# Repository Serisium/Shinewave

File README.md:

# Overview

Shinewave is a program for the ATtiny85 microcontroller that allows it to decode a live GameCube controller signal and reactively power RGB LEDs based on button inputs.

[More information](http://electricexploits.net/shinewave/)

[Video](https://www.youtube.com/watch?v=1U4EOI_aFdc)

## Installation & Usage

Shinewave has been written on a Linux system and requires the full avr-gcc toolchain to make.

In Debian, the toolchain can be set up with the following commands.

	sudo apt-get install gcc-avr avr-libc avrdude

Then, download the repository to your local machine. 

	git clone git@github.com:GGreenwood/Shinewave.git
    git checkout t85

To build the project, just run `make`, or `make flash` to build and program. You'll probably need to chance the `PROGRAMMER` line in `Makefile` in order to program it directly.

## Wiring

## Dependencies

This project depends on one library

* Josh Levine's simple [NeoPixel Demo](https://github.com/bigjosh/SimpleNeoPixelDemo) library

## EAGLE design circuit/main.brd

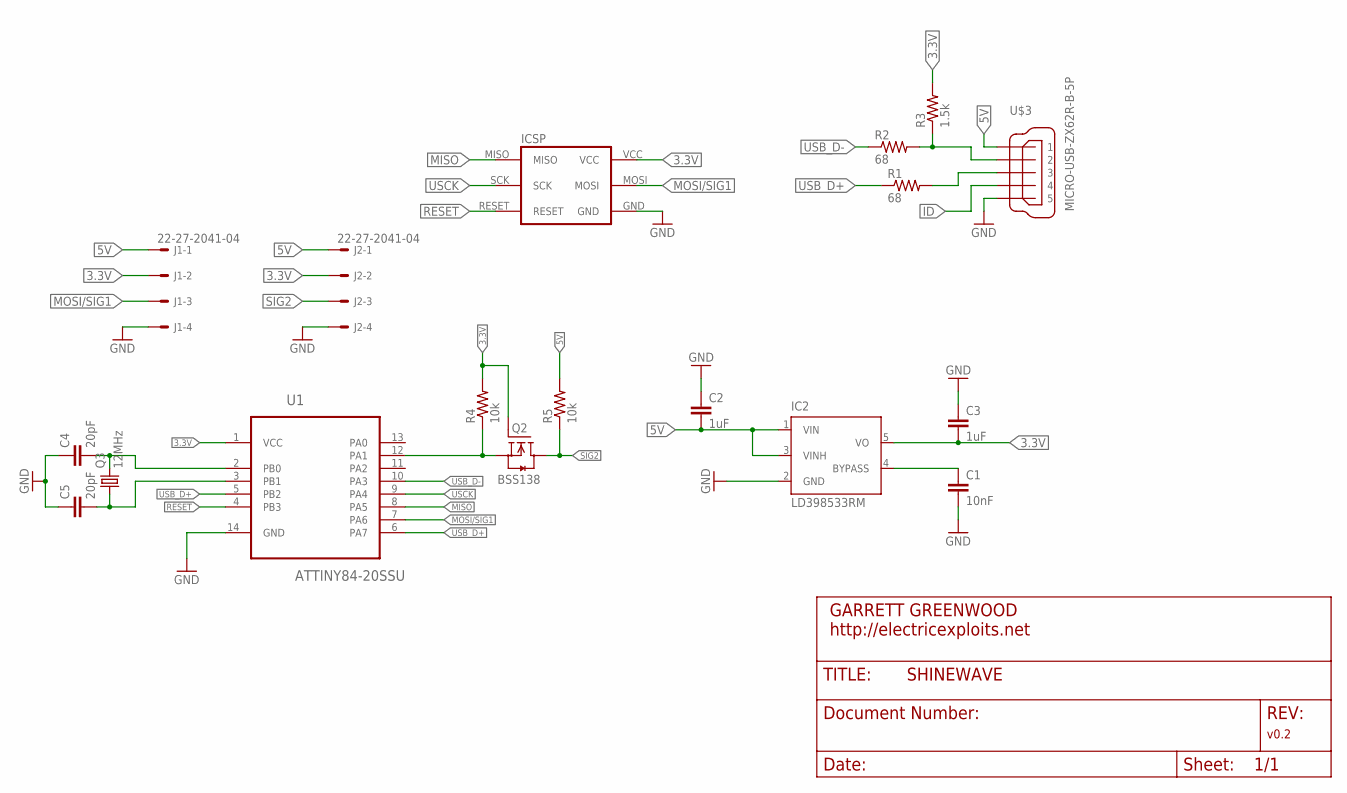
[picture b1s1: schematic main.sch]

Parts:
C1: 10nF; C0603
C2, C3: 1uF; C0603
C4, C5: 20pF; C0603
IC2: LD398533RM; SOT23-5L
J1, J2: 22-27-2041-04; 6410-04
Q2: BSS138; SOT23
Q3: 12MHz; CTS406
R1, R2: 68; R0603
R3: 1.5k; R0603
R4, R5: 10k; R0603
U1: ATTINY84-20SSU; SOIC127P600X175-14N
U$1: ICSP_POGO_INTERFACE; ICSP_SMD
U$3: MICRO-USB-ZX62R-B-5P; ZX62R-B-5P

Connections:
3.3V: C3.2, IC2.5 (VO), J1.2, J2.2, Q2.1 (G), R3.2, R4.2, U1.1 (VCC), U$1.VCC
5V: C2.2, IC2.1 (VIN), IC2.3 (VINH), J1.1, J2.1, R5.2, U$3.1
GND: C1.2, C2.1, C3.1, C4.1, C5.1, IC2.2 (GND), J1.4, J2.4, U1.14 (GND), U$1.GND, U$3.5
ID: U$3.4
MISO: U1.8 (PA5), U$1.MISO
MOSI/SIG1: J1.3, U1.7 (PA6), U$1.MOSI
unnamed: Q2.2 (S), R4.1, U1.12 (PA1)
unnamed: R2.2, R3.1, U$3.2
unnamed: C1.1, IC2.4 (BYPASS)
unnamed: R1.2, U$3.3
RESET: U1.4 (PB3), U$1.RESET
SIG2: J2.3, Q2.3 (D), R5.1
USB_D+: R1.1, U1.5 (PB2), U1.6 (PA7)
USB_D-: R2.1, U1.10 (PA3)
USCK: U1.9 (PA4), U$1.SCK
XTAL1: C4.2, Q3.3 (2), U1.2 (PB0)
XTAL2: C5.2, Q3.1, U1.3 (PB1)

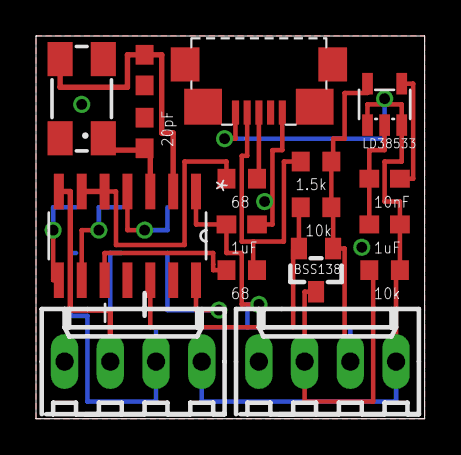
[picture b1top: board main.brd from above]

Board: 2 copper layers, 21.6 x 21.3 mm, 18 parts (0 on the bottom side), 16 nets.

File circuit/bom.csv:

"Part";"Value";"Device";"Package";"Description";"MF";"MPN";"OC_FARNELL";"OC_NEWARK";"PACKAGE";"SUPPLIER";
"C1";"10nF";"C-EUC0603";"C0603";"CAPACITOR, European symbol";"";"";"";"";"";"";
"C2";"1uF";"C-EUC0603";"C0603";"CAPACITOR, European symbol";"";"";"";"";"";"";
"C3";"1uF";"C-EUC0603";"C0603";"CAPACITOR, European symbol";"";"";"";"";"";"";
"C4";"20pF";"C-EUC0603";"C0603";"CAPACITOR, European symbol";"";"";"";"";"";"";
"C5";"20pF";"C-EUC0603";"C0603";"CAPACITOR, European symbol";"";"";"";"";"";"";
"IC2";"LD398533RM";"LD398533RM";"SOT23-5L";"Ultra low drop and low noise BiCMOS voltage regulators";"";"";"";"";"";"";
"J1";"22-27-2041-04";"22-27-2041-04";"6410-04";"CONNECTOR";"";"";"unknown";"unknown";"";"";
"J2";"22-27-2041-04";"22-27-2041-04";"6410-04";"CONNECTOR";"";"";"unknown";"unknown";"";"";
"Q2";"BSS138";"BSS138";"SOT23";"Fairchild Semiconductors BSS138 N-Channel Logic Level Enhancement Mode Field Effect Transistor";"";"";"";"";"";"";
"Q3";"12MHz";"CRYSTALCTS406";"CTS406";"CRYSTAL";"";"";"unknown";"unknown";"";"";
"R1";"68";"R-US_R0603";"R0603";"RESISTOR, American symbol";"";"";"";"";"";"";
"R2";"68";"R-US_R0603";"R0603";"RESISTOR, American symbol";"";"";"";"";"";"";
"R3";"1.5k";"R-US_R0603";"R0603";"RESISTOR, American symbol";"";"";"";"";"";"";
"R4";"10k";"R-US_R0603";"R0603";"RESISTOR, American symbol";"";"";"";"";"";"";
"R5";"10k";"R-US_R0603";"R0603";"RESISTOR, American symbol";"";"";"";"";"";"";
"U$1";"ICSP_POGO_INTERFACE";"ICSP_POGO_INTERFACE";"ICSP_SMD";"ICSP pads for programming over a pogo-pin interface.";"";"";"";"";"";"";
"U$3";"MICRO-USB-ZX62R-B-5P";"MICRO-USB-ZX62R-B-5P";"ZX62R-B-5P";"Hirose Micro USB Connector";"";"";"";"";"";"";
"U1";"ATTINY84-20SSU";"ATTINY84-20SSU";"SOIC127P600X175-14N";"8-bit Microcontroller with Bytes In-System Programmable Flash";"";"ATTINY84-20SSU";"1636955";"03P2040";"SOIC-14";"Atmel";

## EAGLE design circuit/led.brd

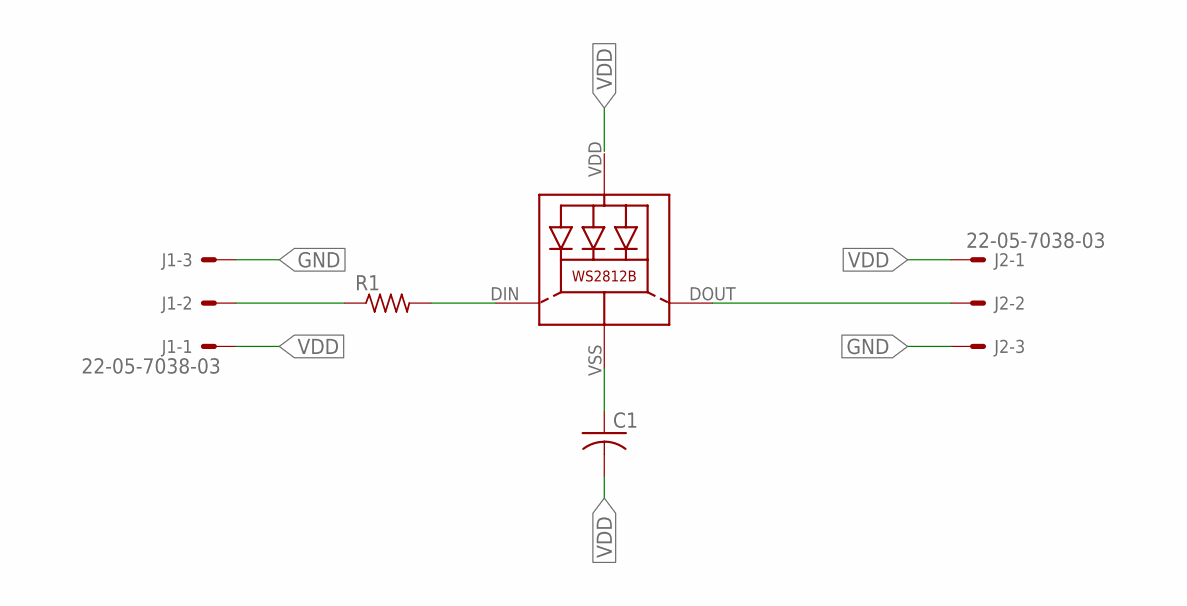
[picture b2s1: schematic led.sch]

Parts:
C1: C-USC0603; C0603
J1, J2: 22-05-7038-03; 7395-03
LED1: WS2812B
R1: R-US_R0603; R0603

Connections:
GND: C1.1, J1.3, J2.3, LED1.VSS (GND)
unnamed: J1.2, R1.1
unnamed: LED1.DIN (DI), R1.2
unnamed: J2.2, LED1.DOUT (DO)
VDD: C1.2, J1.1, J2.1, LED1.VDD

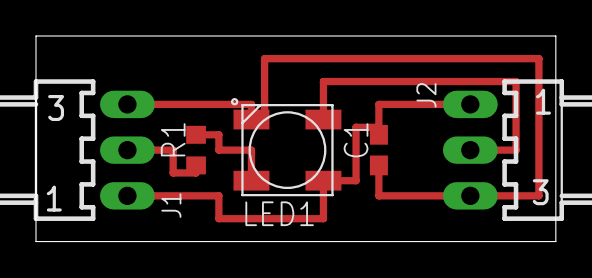
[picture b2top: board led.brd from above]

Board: 2 copper layers, 28.9 x 11.4 mm, 5 parts (0 on the bottom side), 5 nets.

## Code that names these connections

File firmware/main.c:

#include <avr/interrupt.h>
#include <avr/io.h>
#include <avr/wdt.h>
#include <stdint.h>
#include <util/delay.h>

//#include "libs/Neopixel.h"
#include "controller.h"
#include "usb.h"

#define DEBUG_MATCH 0   // Enable PIN_TIMER toggle on timer match. Interferes with USB
#define GCN_RETRY_LIMIT 5   // Number of times to retry the GCN signal line

#define PIN_DEBUG PA2
#define PIN_GC    PA6   // Needs to be connected to (DI)
//#define PIN_TIMER PA7   // Needs to be connected to (OC0B). Displays compare match toggles if DEBUG_MATCH is set

#define GET_BIT(TGT, PIN)    ((TGT) & (1 << (PIN))) 
#define SET_BIT(TGT, PIN)    do { TGT |=  (1 << (PIN)); } while(0)
#define CLEAR_BIT(TGT, PIN)  do { TGT &= ~(1 << (PIN)); } while(0)
#define TOGGLE_BIT(TGT, PIN) do { TGT ^=  (1 << (PIN)); } while(0)

#define SEND_ZERO()        do { CLEAR_BIT(PORTA, PIN_GC); _delay_us(3); SET_BIT(PORTA, PIN_GC); _delay_us(1); } while(0)
#define SEND_ONE()         do { CLEAR_BIT(PORTA, PIN_GC); _delay_us(1); SET_BIT(PORTA, PIN_GC); _delay_us(3); } while(0)

void setup_pins(void) {
    CLEAR_BIT(DDRA, PIN_GC);		// Set PIN_GC as input, GCN data signal
    SET_BIT(PORTA, PIN_GC);		    // Enable pull-up resistor on PIN_GC
    SET_BIT(DDRA, PIN_DEBUG);       // Set PIN_DEBUG as output for debugging

    // Ensure that USB pins are inputs with pullup resistor disabled
    CLEAR_BIT(DDRB, PB2);
    CLEAR_BIT(DDRA, PA3);
    CLEAR_BIT(DDRA, PA7);
    CLEAR_BIT(PORTB, PB2);
    CLEAR_BIT(PORTA, PA3);
    CLEAR_BIT(PORTA, PA7);

    #if DEBUG_MATCH == 1
    SET_BIT(DDRA, PIN_TIMER);       // Set PIN_TIMER as output for compare matches
    #endif
    //ledsetup();
}

void enable_timer0(void) {
    TCNT0 = 0;
    TIFR0 = 0xff;                   // Reset interrupt flags

    #if DEBUG_MATCH == 1
    // Set 0C0B(PA7) to toggle on match(COM0B=01)
    SET_BIT(TCCR0A, COM0B0);
    #endif

    // Enable Timer/Counter0 module at no prescaler
    SET_BIT(TCCR0B, CS00);
}

void disable_timer0(void) {
    #if DEBUG_MATCH == 1
    // Set 0C0B(PA7) to toggle on match(COM0B=01)
    CLEAR_BIT(TCCR0A, COM0B0);
    #endif

    // Disable Timer/Counter0 module
    CLEAR_BIT(TCCR0B, CS00);        
}

// Set Timer/Counter0 in normal mode(WGM=000)
void setup_timer0(void) {
    disable_timer0();

    // Set compare match to signal critical point(2us)
    OCR0A = 2e-6 * F_CPU;   // Triggers USI clock source

    #if DEBUG_MATCH == 1
    OCR0B = 2e-6 * F_CPU;   // Triggers debug toggle
    #endif
}

void enable_usi(void) {
    // Enable Universal Serial Module in Two-wire mode(USIWM=10)
    SET_BIT(USICR, USIWM1);
}

void disable_usi(void) {
    // Disable Universal Serial Module
    SET_BIT(USICR, USIWM1);
}

void setup_usi(void) {
    // Set clock source to Timer/Counter0 Compare Match(USICS=01)
    SET_BIT(USICR, USICS0);
}

void setup_usb(void) {
    cli();
    wdt_enable(WDTO_1S);    // enable 1s watchdog timer
    usbInit();

    usbDeviceDisconnect();  // enforce re-enumeration
    uint8_t i;
    for(i = 0; i<250; i++) {
        wdt_reset();
        _delay_ms(2);
    }
    usbDeviceConnect();
    sei();
}

void init_controller(void) {
    SET_BIT(PORTA, PIN_GC);         // Set positive output on PIN_GC
    SET_BIT(DDRA, PIN_GC);          // Set PIN_GC as output

    // Send controller init message (000000001)
    for(uint8_t bit = 0; bit < 8; bit++) {
        SEND_ZERO();
    }
    SEND_ONE();

    CLEAR_BIT(DDRA, PIN_GC);        // Set PIN_GC as input
}

uint8_t request_message(uint8_t *message_buffer) {
    //uint8_t cur_byte = 0;

    //USISR = 0b11101000;             // Reset USI Interrupt flags and set timer value to 8
    //disable_usi();
    //disable_timer0();

    CLEAR_BIT(PORTA, PIN_DEBUG);
    SET_BIT(PORTA, PIN_DEBUG);
    CLEAR_BIT(PORTA, PIN_DEBUG);
    
    SET_BIT(PORTA, PIN_GC);
    SET_BIT(DDRA, PIN_GC);          // Set PIN_GC as output

    asm volatile(
            ".rept 3 \n\t"
                "cbi %[port], %[bit] \n\t"
                ".rept 34 \n\t"
                    "nop \n\t"
                ".endr \n\t"
                "sbi %[port], %[bit] \n\t"
                ".rept 10 \n\t"
                    "nop \n\t"
                ".endr \n\t" 
                "cbi %[port], %[bit] \n\t"
                ".rept 10 \n\t"
                    "nop \n\t"
                ".endr \n\t"
                "sbi %[port], %[bit] \n\t"
                ".rept 34 \n\t"
                    "nop \n\t"
                ".endr \n\t" 
            ".endr \n\t"
            ".rept 18 \n\t"
                "cbi %[port], %[bit] \n\t"
                ".rept 34 \n\t"
                    "nop \n\t"
                ".endr \n\t"
                "sbi %[port], %[bit] \n\t"
                ".rept 10 \n\t"
                    "nop \n\t"
                ".endr \n\t"
            ".endr \n\t"
            "cbi %[port], %[bit] \n\t"
            ".rept 10 \n\t"
                "nop \n\t"
            ".endr \n\t"
            "sbi %[port], %[bit] \n\t"
            ".rept 34 \n\t"
                "nop \n\t"
            ".endr \n\t"
            :: 
            [port]      "I" (_SFR_IO_ADDR(PORTA)),
            [bit]       "I" (PA6)
        );

    SET_BIT(PORTA, PIN_GC);
    CLEAR_BIT(DDRA, PIN_GC);        // Set PIN_GC as input
    
    return 1;
    /*

    // Send controller data request
    SEND_ZERO(); SEND_ONE();  SEND_ZERO(); SEND_ONE();  SEND_ZERO(); SEND_ONE();  SEND_ZERO(); SEND_ZERO(); 
    SEND_ZERO(); SEND_ZERO(); SEND_ZERO(); SEND_ZERO(); SEND_ZERO(); SEND_ZERO(); SEND_ZERO(); SEND_ZERO();
    SEND_ZERO(); SEND_ZERO(); SEND_ZERO(); SEND_ZERO(); SEND_ZERO(); SEND_ZERO(); SEND_ZERO(); SEND_ZERO(); 
    SEND_ONE();

    SET_BIT(PORTA, PIN_GC);
    CLEAR_BIT(DDRA, PIN_GC);        // Set PIN_GC as input

    // Start reading the message
    enable_usi();
    enable_timer0();
    while(1) {
        // Wait for signal to go low
        while(GET_BIT(PINA, PIN_GC)) {
            // Catch a timer overflow as an exit condition
            // This occurs if the signal is high for > 255 cycles
            if(GET_BIT(TIFR0, TOV0)) {
                // Exit condition
                disable_usi();

                // Wait for the timer to overflow and loop once, fixes 'every other' corruption
                while(TCNT0 < 24) {}

                // Check if there's no signal on the line
                if(cur_byte == 0) {
                    SET_BIT(PORTA, PIN_DEBUG);
                    CLEAR_BIT(PORTA, PIN_DEBUG);
                    return 0;
                }

                disable_timer0();
                return 1;
            }
        }
        // Reset Timer0, a little higher than 0 to account for polling delay
        TCNT0 = 5;

        // Check if a byte has passed
        if(GET_BIT(USISR, USIOIF)) {
            // Skip the counter to 8 of 16
            SET_BIT(USISR, USICNT3);    

            // Store the byte from the serial buffer
            message_buffer[cur_byte] = USIBR;
            cur_byte++;

            // Toggle the debug pin
            //TOGGLE_BIT(PORTA, PIN_DEBUG);

            // Clear the overflow counter
            SET_BIT(USISR, USIOIF);
        }

        // Make sure signal is high before looping
        // Hardware should pull up DIN or risk an infinite loop
        while(!GET_BIT(PINA, PIN_GC)) {}
    }
    */

    // Unreachable code
    return 0;
}

int main(void)
{
    setup_pins();
    //setup_timer0();
    //setup_usi();
    setup_usb();
    //init_controller();

    uint8_t retry_count = 0;

    uint8_t message_buffer[8] = {0};
    Keyboard *keyboard = (Keyboard*)message_buffer;

    /*
    while(1) {
        request_message(message_buffer);
        for(uint8_t i = 0; i < 16; ++i) {
            wdt_reset();
            usbPoll();
            _delay_ms(1);
        }
    }
    */

    while(1) {
        usbPoll();
        wdt_reset();

        if(usbInterruptIsReady()) {
            // Zero out input array
            for(uint8_t i = 0; i < 8; ++i) {
                message_buffer[i] = 0x00;
            }
            // Try to grab the controller state
            retry_count = GCN_RETRY_LIMIT;
            while(retry_count--) {
                if(request_message(message_buffer)) {
                    build_report(keyboard, &reportBuffer);
                    usbSetInterrupt((void *)&reportBuffer, sizeof(reportBuffer));
                    break;
                }

                _delay_us(50);
            }
        }
    }
}

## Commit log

2015-06-13 Added proof of concept C code implementing mock animation and protothreads
2015-06-18 Added compilation procedure
2015-06-18 Removed swap file
2015-06-18 Wrote proper Makefile
2015-06-24 Rewrote controller reading code to use the Analog Comparator
2015-06-27 Fixed endianness of controller POC definition
2015-06-28 Started work on animation protothread and controller state wrapper
2015-06-29 Added smooth animation lookups and a jump thread
2015-06-30 Added sawtooth function and idle animation
2015-06-30 Fixed jump animation
2015-07-03 Moved saw macro into a function and omitted descending functions
2015-07-03 Delayed idle animation until the controller is actually idle
2015-07-03 Controller can now jump out of neutral
2015-07-03 Controller can now down-air
2015-07-03 Added taunt
2015-07-04 Made down-air shine cancellable
2015-07-13 Added eight brightness levels
2015-07-15 Started work on state machine proof of concept
2015-07-15 fixed output
2015-07-16 progress, or something
2015-07-16 more progress, thanks reid for help
2015-07-16 WEEEEEEEEEEEEEE
2015-07-16 made the code neater and left notes for the morning
2015-07-17 Added exit condition on max frame
2015-07-17 Added single exit condition
2015-08-02 Added comments
2015-08-02 Moved proof of concept demos to its own repo
2015-08-27 added delay loop; needs tested
2015-08-30 Updated project name and added make fuse command
2015-08-31 Rewrote EVERYTHING
2015-08-31 Reduced timer complexity
2015-08-31 Testing control stick driven colors
2015-09-01 Integrated Controller convenience class
2015-09-01 Added reactive wait times; works on GC/Wii
2015-09-02 Implemented new animation state machine, courtesy @JustANull
2015-09-13 Updated indentation
2015-09-21 Microcontroller can now request controller state
2015-09-21 Gamecube controller is now a mouse
2015-09-22 Gamecube controller is now a joystick (still labeled as mouse)
2015-09-26 Removed old project name
2015-10-13 Modified code to run at 3.3V/12.8MHz rather than 5V/16MHz
2015-10-13 Removed compiled object files
2015-10-13 Fixed message stutter
2015-10-31 Spookified!
2015-11-06 Migrated to ATtiny84 and stripped code
2015-11-06 Changed folder layout
2015-11-07 added controller code and fixed stutter; is silly
2015-11-07 Cleaned up* code
2015-11-09 Add 5-light support. Add patterns. Break API.
    5-light support means that API consumers will
    need to change how they use it, so I took the
    opportunity to change the method signature more
    than just changing to a pointer, with output
    coming first in the signature in my preferred
    style.
2015-11-09 Remove stdio dependency. Attempt optimization.
    As with most of the code in this, my optimization
    has never been tested, but I'm rather sure that it
    is correct. More testing will follow, but as of this
    commit this code may break the build.
2015-11-09 Low bit is left light, initialize Machine fully
2015-12-05 Added delay_x library to simplify GCN transmission macros
2015-12-19 Refactored usb.c and added timer behavior for new SPI implementation
2015-12-19 Cleaned up comments
2015-12-20 Removed Analog Comparator functionality, moved GC signal to PA6(DI)
2015-12-22 Removed unused delay_x library
2015-12-22 Added USI code in Two-Wire mode
2015-12-23 Fixed half-broken behavior, am still spooked by the R button
2016-01-02 some stability improvements
2016-01-13 'fixed' issue with R button by adding a retry loop
2016-01-27 Added v0.2 of PCB
2016-02-09 Added EAGLE files for v0.2 PCB
2016-02-09 Updated pins and fuses for PCB prototype v0.2
2016-02-09 Fixed stack overflow when no controller is connected by adding a retry limit
2016-02-10 Added LED test code
2016-02-29 Updated fuses for bootloader
2016-02-29 added micronucleus bootloader
2016-03-06 Cleaned up firmware
2016-03-06 Updated README with Arch instructions
2016-03-06 Added schematic and board images
2016-03-06 Updated v0.2 schematics to include title frame
2016-03-06 Added controller image
2016-03-06 Updated README with build instructions
2016-03-06 Added proper PID/VID pair
2016-03-06 Configured micronucleus some more
2016-03-06 Added micronucleus gitignore
2016-03-06 Create License.md
    Added MIT License
2016-03-06 Added links to README
2016-03-06 Fixed newlines
2016-03-21 Updated gitignore and README
2016-03-21 Updated gitignore
2016-03-23 Relicense state machine; Increase modularization
    Broke up dependent bits so they aren't all cluttering the same file. The
    same process still needs to be applied to the remainder of the
    statemachine file if it can be usefully detangled without issue.
    I hereby license past and future contributions to GGreenwood's Shinewave
    project under the MIT License.
2016-03-23 Reorder commits and include stdint where it wasn't
    It's cleaner for files to include all of their dependencies and to do it
    in a predictable order. Move towards doing that.
2016-03-23 Fix error from splitting files
2016-03-24 Added test code for discovering ASCII scan codes and breadboard fuse settings
2016-03-26 Added proper Eagle gitignore
2016-03-26 gitignore is now working
2016-03-26 Restored original gitignore lines
2016-03-26 Removed duplicate .gitignore for EAGLE lock files
2016-03-26 Initial run of include-what-you-use
    With a couple of edits to fit the surrounding style. Hopefully makes
    files more accurate in immediate identification of what their
    dependencies are, rather than relying on another header transitively
    including them.
2016-03-26 Make recursively clean
    The current rm command only checks the current directory and the listed
    ones, in particular skipping other subdirectories.
    Perhaps switch this out to something that operates with the Makefile
    variables, avoiding the `find` command entirely?
2016-03-26 Normalize line endings, trailing whitespace
    Unix newlines, in particular
2016-04-10 Updated circuit for Shinewave v0.3
2016-04-10 removed duplicate circuit files
2016-04-10 Made changes to button/analog layout for better support with Rivals of Aether
2016-04-16 Gutted USB joystick code and adjusted parameters to listen to the console
2016-04-16 Added sample PCB for mountable LEDs
2016-04-16 Rewrote lookup function and added animation stubs
2016-04-16 Rewrote animation handling to be contained in a Satus struct
2016-04-17 Added grab animation
2016-04-17 Added ice block and jump states
2016-04-18 Disabled brightness correction and added directional sweeps
2016-04-18 Added directional smashes, aerials, and tilts
2016-04-18 Added pink echo on A-attacks
2016-04-19 Added side-b and wobble detection
2016-04-19 added wobbling animation
2016-04-19 Reduced code size and added idle animation
2016-04-19 Slowed idle animation
2016-04-19 Fixed equality test
2016-04-20 Fixed wobble animation
2016-05-14 Added brightness controls
2016-06-07 Updated circuit for Shinewave v0.3.1
2016-06-07 Reverted wobbles' code being pushed to the main branch
2016-06-20 Purple test color for DooS customs
2016-06-20 Clarified bootloader settings
2016-07-01 Updated schematics
2016-08-16 Basic ASCII Keyboard adapter support written
2016-08-16 Mapped the rest of the keys
2016-08-16 Ineffecient assembly polling prototype
2017-04-17 Cleaned up ATTiny85 codebase, from version 0.1.1
2017-04-17 removed old project name from README
2017-04-17 Fixed controller reading and implemented Controller convenience class
2017-07-27 Fixed typo in makefile
2017-07-30 fixed animation struct initialization
2017-07-30 First routine prototype
2017-07-30 Started work on new animation layout
2017-08-02 Added Routine concept and seperated routines into their own files
2017-08-05 [WIP] improving routine abilities, broken atm
2017-08-24 muffin bros animation
2017-08-26 Revert "muffin bros animation"
    This reverts commit bc1e6d1c79a7105dbc30e639736b50aa3428f67f.
2017-08-26 Fixed idle flashing bug
2017-08-26 fixed shine loop

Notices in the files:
parts and their libraries:
m-pad-2.1: License : GNU General Public License version 2 (see bottom)
